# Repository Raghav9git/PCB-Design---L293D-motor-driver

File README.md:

# L293D Motor Driver PCB with Integrated IR Sensor

## Overview

This project presents the design and development of a custom PCB integrating the L293D dual H-Bridge motor driver IC with an onboard IR sensor interface for robotic motion control applications.

The board is designed to provide a compact and reliable motor driving solution for small robotics platforms using DC motors.

---

## Tools & Software Used

- KiCad (Schematic Capture and PCB Layout)
- ERC and DRC validation tools
- 2-layer PCB design
- KiCad 3D Viewer for mechanical verification

---

## Hardware Components

- L293D Dual H-Bridge Motor Driver IC
- IR Sensor module interface
- DC motor output terminals (Motor A and Motor B)
- Screw terminal blocks
- Decoupling capacitors
- Motor power supply input
- 5V logic supply input

---

## System Architecture

The PCB integrates:

- Dual motor control outputs
- Logic control pins (IN1, IN2, IN3, IN4, ENA, ENB)
- IR sensor signal input routed to an external microcontroller
- Separate motor supply (Vmotor) and logic supply (Vcc)
- Common ground with appropriate decoupling

The board is designed to interface with external microcontrollers such as Arduino or ESP32 for implementing motor control logic.

---

## Working Principle

The L293D IC functions as a dual H-Bridge motor driver enabling:

- Forward rotation
- Reverse rotation
- Brake mode
- PWM-based speed control via enable pins

The IR sensor output can be connected to a microcontroller to enable:

- Obstacle detection
- Line following logic
- Basic autonomous navigation

---

## PCB Design Highlights

- Appropriate trace width selection for motor current handling
- Decoupling capacitors placed close to IC power pins
- Separation of power and logic routing
- Compact layout to reduce signal noise
- Clearly labeled input and output terminals

---

## Applications

- Obstacle avoidance robots
- Line following robots
- Small autonomous vehicles
- Robotics prototyping platforms

---

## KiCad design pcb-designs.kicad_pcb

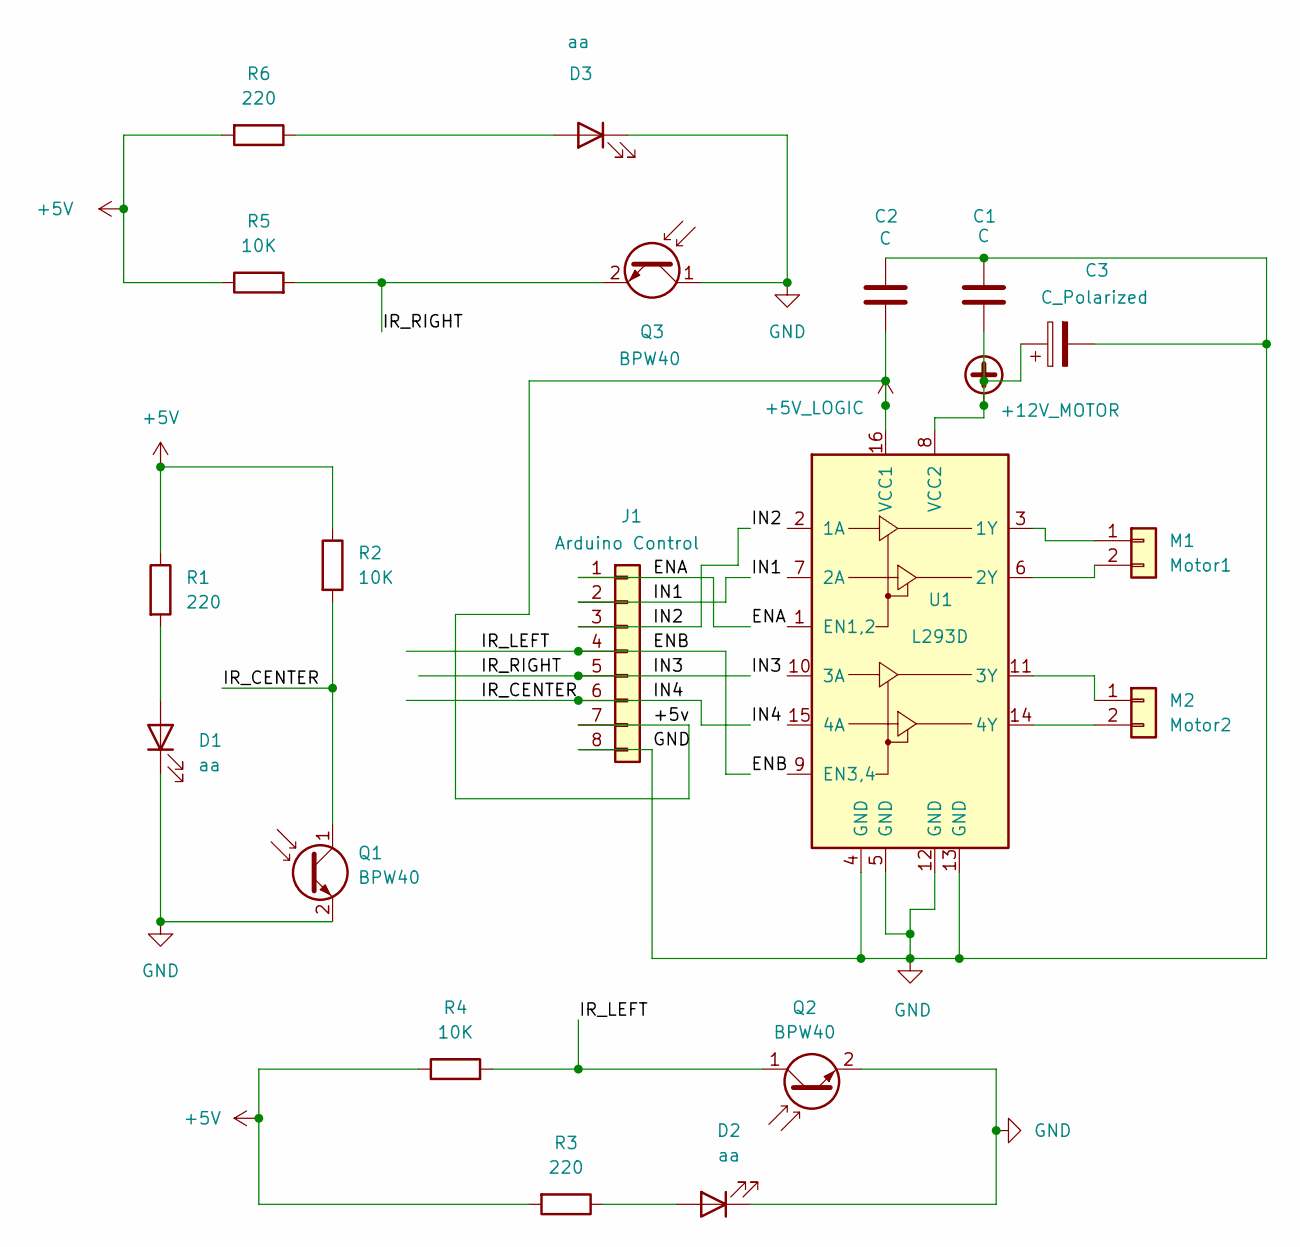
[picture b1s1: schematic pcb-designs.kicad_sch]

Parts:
C1, C2: C; C_Disc_D5.0mm_W2.5mm_P5.00mm
C3: C_Polarized; CP_Radial_D5.0mm_P2.00mm
D1, D2, D3: aa; LED_D5.0mm
J1: Arduino Control; PinHeader_1x08_P2.54mm_Vertical
M1: Motor1; TerminalBlock_Degson_DG250-3.5-02P_1x02_P3.50mm_45Degree
M2: Motor2; TerminalBlock_Degson_DG250-3.5-02P_1x02_P3.50mm_45Degree
Q1, Q2, Q3: BPW40; LED_D5.0mm_Clear
R1, R3, R6: 220; R_Axial_DIN0207_L6.3mm_D2.5mm_P7.62mm_Horizontal
R2, R4, R5: 10K; R_Axial_DIN0207_L6.3mm_D2.5mm_P7.62mm_Horizontal
U1: L293D; DIP-16_W7.62mm

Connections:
+5V: R1.1, R2.1, R3.2, R4.1, R5.1, R6.2
+5V_LOGIC: C2.2, J1.7, U1.16 (VCC1)
+12V_MOTOR: C1.2, C3.1, U1.8 (VCC2)
/ENA: J1.1
/ENB: J1.4, Q2.1 (C), R4.2
/IN1: J1.2
/IN2: J1.3
/IN3: J1.5, Q3.2 (E), R5.2
/IN4: J1.6, Q1.1 (C), R2.2
GND: C1.1, C2.1, C3.2, D1.1 (K), D2.1 (K), D3.1 (K), J1.8, Q1.2 (E), Q2.2 (E), Q3.1 (C), U1.4 (GND), U1.5 (GND), U1.12 (GND), U1.13 (GND)
unnamed: D1.2 (A), R1.2
unnamed: D2.2 (A), R3.1
unnamed: D3.2 (A), R6.1
unnamed: M1.1, U1.3 (1Y)
unnamed: M1.2, U1.6 (2Y)
unnamed: M2.1, U1.11 (3Y)
unnamed: M2.2, U1.14 (4Y)

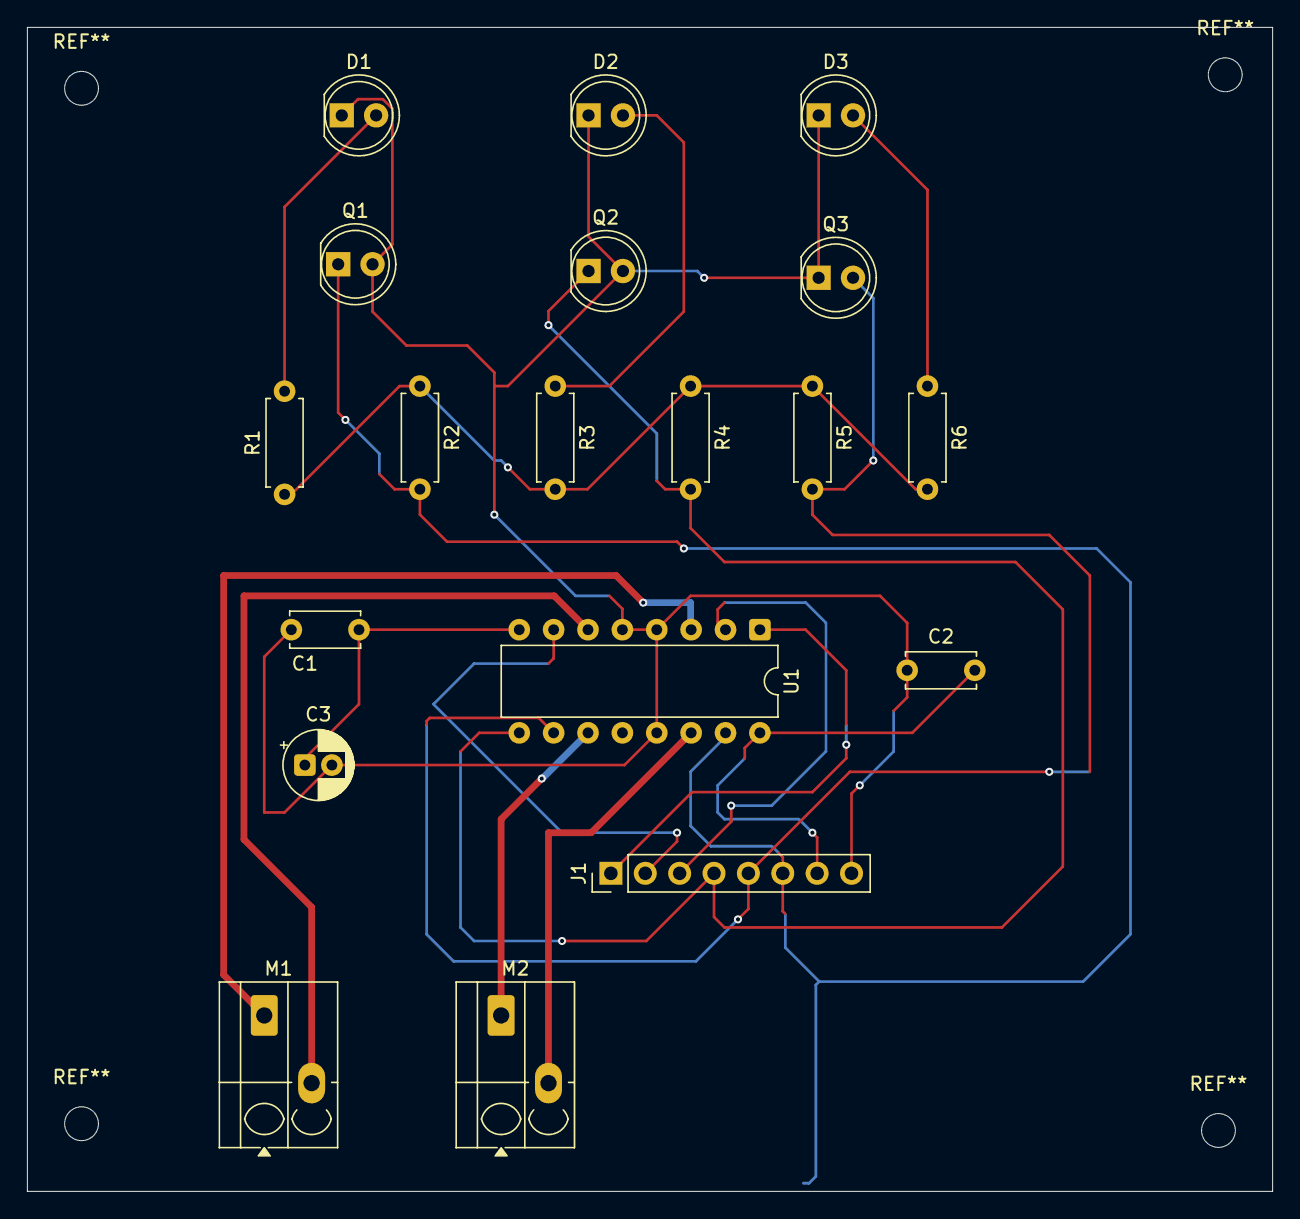
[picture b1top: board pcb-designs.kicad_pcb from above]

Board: 2 copper layers, 92.0 x 86.0 mm, 19 parts (0 on the bottom side), 14 nets.

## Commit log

2026-02-25 Rename Screenshot 2026-01-31 171755.png to Schematic
2026-02-25 Rename Screenshot 2026-01-31 171918.png to 3D view
2026-02-25 Rename Screenshot 2026-01-31 172012.png to Layout
2026-06-18 Rename 3D view to 3D view.png
2026-06-18 Rename Layout to Layout.png
2026-06-18 Rename Schematic to Schematic.png
